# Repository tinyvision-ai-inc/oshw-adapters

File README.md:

# oshw-adapters
Various adapters for GPIO, MIPI etc.

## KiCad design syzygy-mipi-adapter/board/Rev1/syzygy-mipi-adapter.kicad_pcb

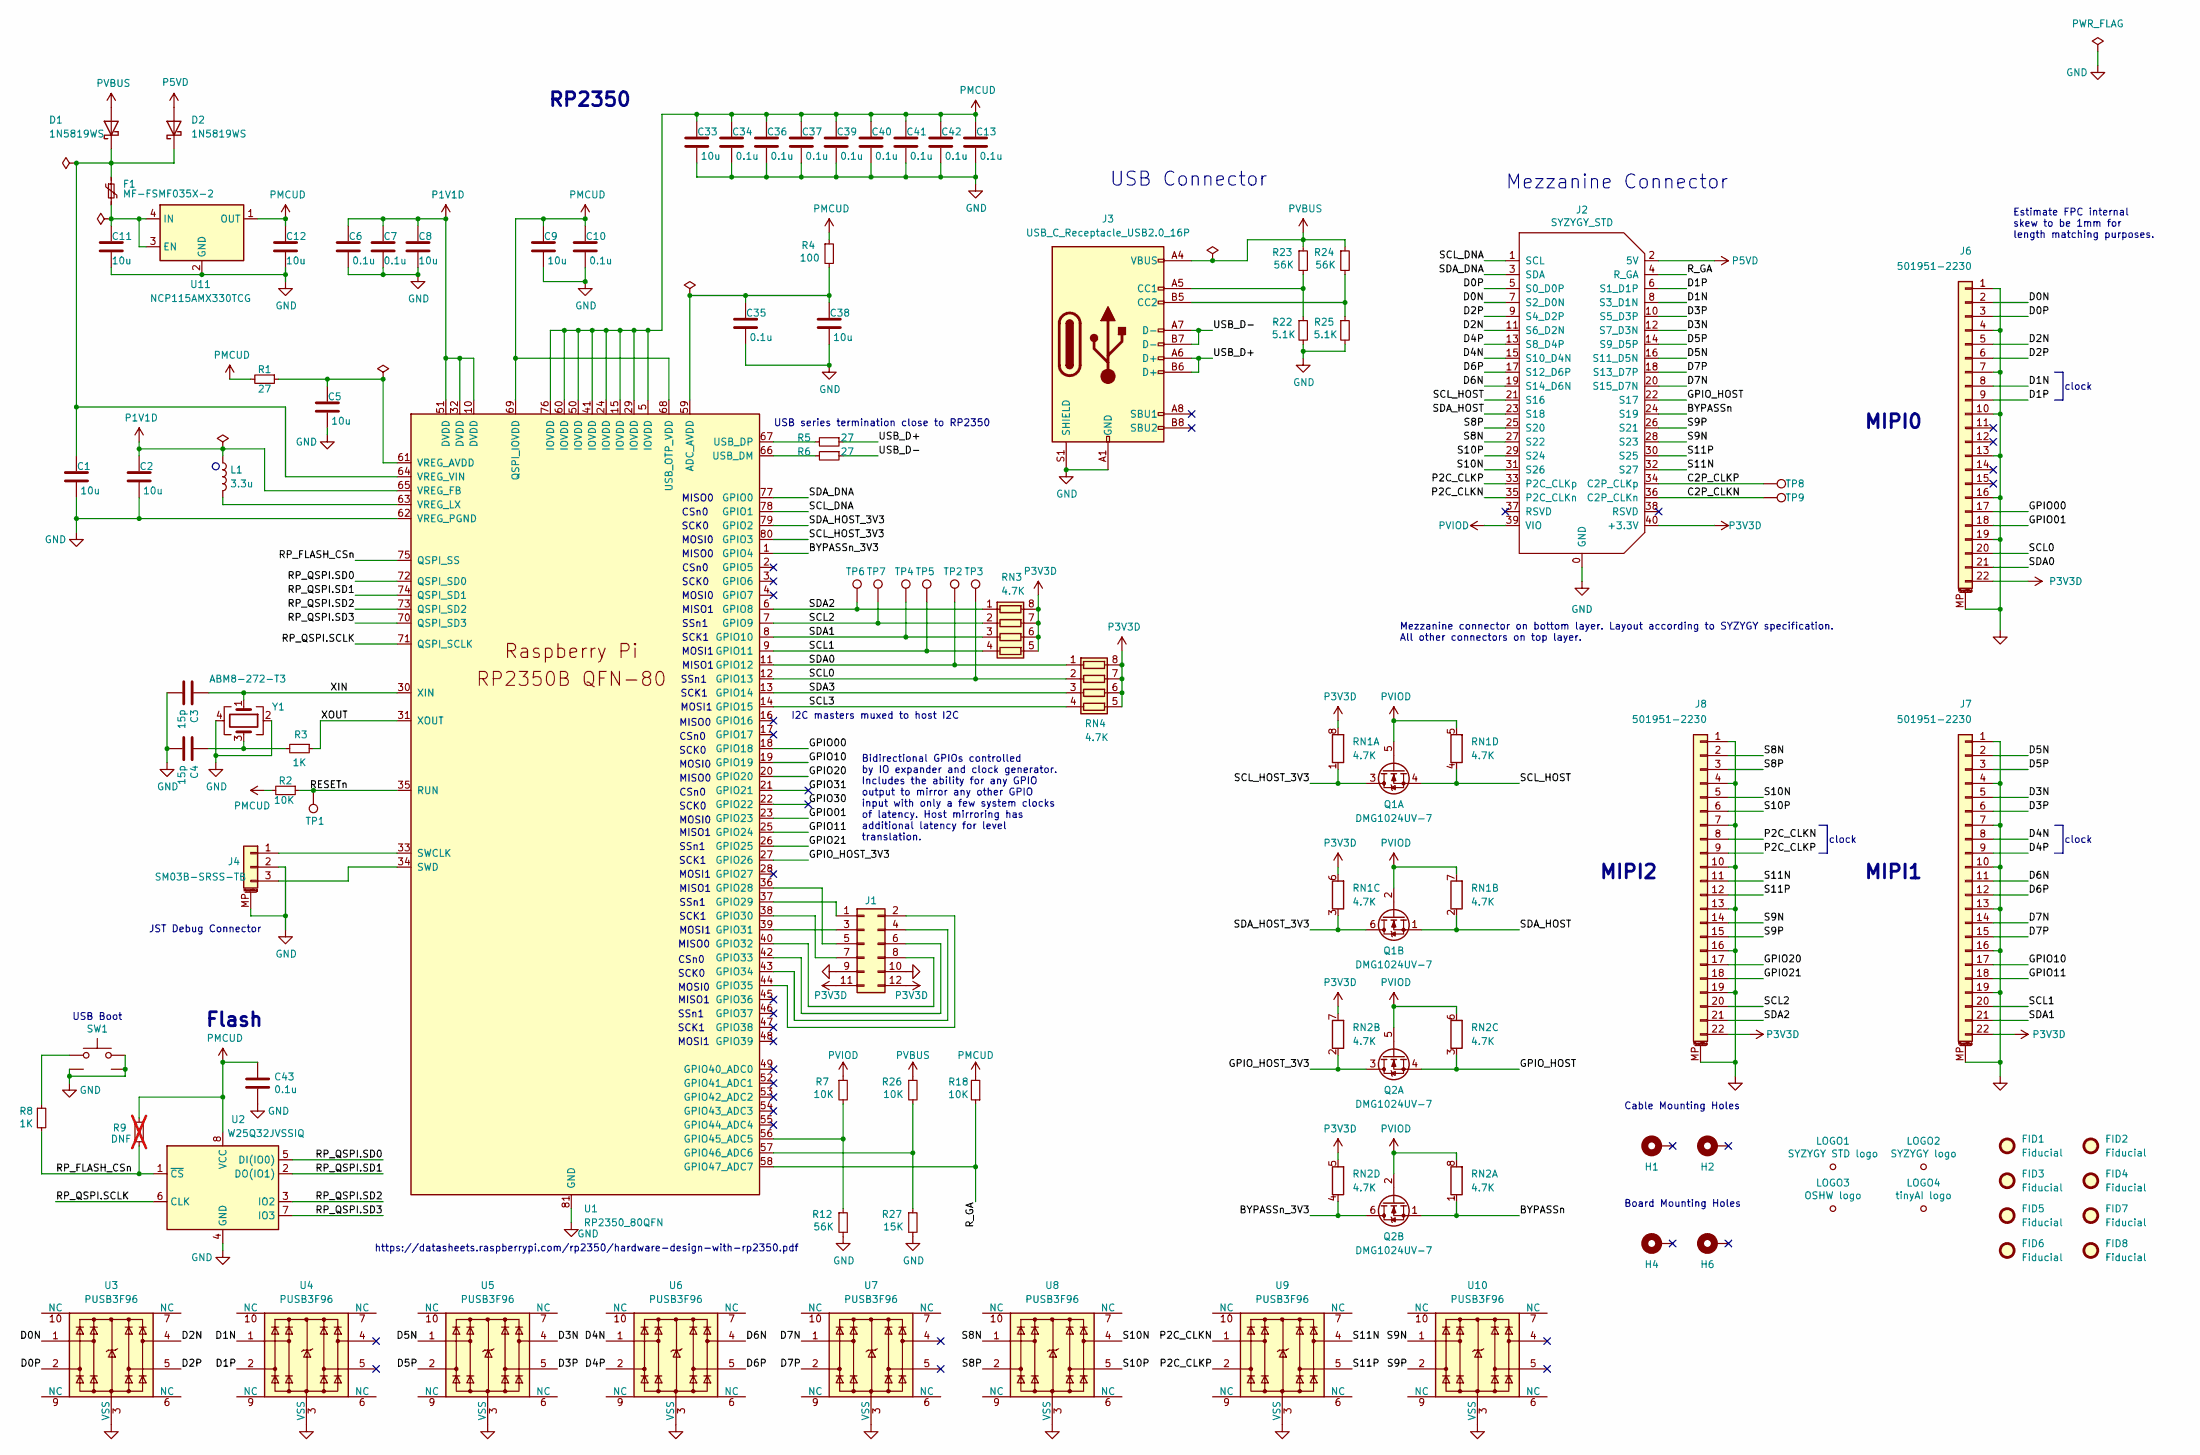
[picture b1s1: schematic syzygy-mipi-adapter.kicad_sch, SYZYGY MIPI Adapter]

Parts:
C1, C2, C5, C8, C9, C11, C12, C33: 10u; C_0402_1005Metric; MPN GRM155R60J475ME87D
C3, C4: 15p; C_0201_0603Metric; MPN GRM1555C1E150JA01D
C6, C7, C10, C13, C34, C35, C36, C37, C39, C40, C41, C42, C43: 0.1u; C_0201_0603Metric; MPN GRM155R71C104KA88J
C38: 10u; C_0402_1005Metric; MPN GRM155R71C104KA88J
D1, D2: 1N5819WS; D_SOD-323
F1: MF-FSMF035X-2; R_0603_1608Metric
FID1, FID2, FID3, FID4, FID5, FID6, FID7, FID8: Fiducial; Fiducial_0.75mm_Mask1.5mm
H1, H2, H4, H6: MountingHole_Pad; MountingHole_3.2mm_M3_6.5mm_Pad_TopBottom
J1: Conn_02x06_Odd_Even; PinHeader_2x06_P2.54mm_Vertical
J2: SYZYGY_STD; QTE-020-01-F-D-A; Manufacturer_PN QTE-020-01-F-D-A
J3: USB_C_Receptacle_USB2.0_16P; USB_C_Receptacle_HRO_TYPE-C-31-M-12
J4: SM03B-SRSS-TB; JST_SH_SM03B-SRSS-TB_1x03-1MP_P1.00mm_Horizontal; MPN SM03B-SRSS-TB
J6, J7, J8: 501951-2230
L1: 3.3u; L_pol_2016; MPN MLP2016H3R3MT0S1
LOGO1: SYZYGY STD logo; SYZYGY_STD_Logo; MPN DNP; Digi-Key_PN DNP
LOGO2: SYZYGY logo; SYZYGY_Logo; MPN DNP; Digi-Key_PN DNP
LOGO3: OSHW logo; OSHW_Dual_0.1_Scale_2140; MPN DNP; Digi-Key_PN DNP
LOGO4: tinyAI logo; tinyAI_4_5mm; MPN DNP; Digi-Key_PN DNP
Q1, Q2: DMG1024UV-7; SOT-563
R1, R5, R6: 27; R_0402_1005Metric; MPN RC0402FR-0727RL
R2, R7, R26: 10K; R_0402_1005Metric; MPN RC0402FR-0727RL
R3, R8: 1K; R_0402_1005Metric; MPN RC0402FR-071KL
R4: 100; R_0402_1005Metric; MPN RC0402FR-0727RL
R9: DNF; R_0402_1005Metric; not fitted
R12, R23, R24: 56K; R_0402_1005Metric; MPN RC0402FR-0727RL
R18: 10K; R_0402_1005Metric
R22, R25: 5.1K; R_0402_1005Metric; MPN RC0402FR-0727RL
R27: 15K; R_0402_1005Metric; MPN RC0402FR-0727RL
RN1, RN2, RN3, RN4: 4.7K; R_Array_Concave_4x0402
SW1: PTS820J25KSMTRLFS
TP1, TP2, TP3, TP4, TP5, TP6, TP7, TP8, TP9: TestPoint; TestPoint_Pad_1.0x1.0mm
U1: RP2350_80QFN; RP2350B_QFN-80_EP_10.573x10.573_Pitch0.4mm
U2: W25Q32JVSSIQ; SOIC-8_5.3x5.3mm_P1.27mm; MPN W25Q32JVSSIQ
U3, U4, U5, U6, U7, U8, U9, U10: PUSB3F96; PUSB3F96X
U11: NCP115AMX330TCG; OnSemi_XDFN4-1EP_1.0x1.0mm_EP0.52x0.52mm
Y1: ABM8-272-T3; Crystal_SMD_3225-4Pin_3.2x2.5mm; MPN ABM8-272-T3

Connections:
/BYPASSn: J2.24 (S19), Q2.1 (S), RN2.1 (R1.1)
/BYPASSn_3V3: Q2.6 (D), RN2.4 (R4.1), U1.1 (GPIO4)
/C2P_CLKN: J2.36 (C2P_CLKn), TP9.1
/C2P_CLKP: J2.34 (C2P_CLKp), TP8.1
/D0N: J2.7 (S2_D0N), J6.2, U3.1
/D0P: J2.5 (S0_D0P), J6.3, U3.2
/D1N: J2.8 (S3_D1N), J6.8, U4.1
/D1P: J2.6 (S1_D1P), J6.9, U4.2
/D2N: J2.11 (S6_D2N), J6.5, U3.4
/D2P: J2.9 (S4_D2P), J6.6, U3.5
/D3N: J2.12 (S7_D3N), J7.5, U5.4
/D3P: J2.10 (S5_D3P), J7.6, U5.5
/D4N: J2.15 (S10_D4N), J7.8, U6.1
/D4P: J2.13 (S8_D4P), J7.9, U6.2
/D5N: J2.16 (S11_D5N), J7.2, U5.1
/D5P: J2.14 (S9_D5P), J7.3, U5.2
/D6N: J2.19 (S14_D6N), J7.11, U6.4
/D6P: J2.17 (S12_D6P), J7.12, U6.5
/D7N: J2.20 (S15_D7N), J7.14, U7.1
/D7P: J2.18 (S13_D7P), J7.15, U7.2
/GPIO00: J6.17, U1.18 (GPIO18)
/GPIO01: J6.18, U1.23 (GPIO23)
/GPIO10: J7.17, U1.19 (GPIO19)
/GPIO11: J7.18, U1.25 (GPIO24)
/GPIO20: J8.17, U1.20 (GPIO20)
/GPIO21: J8.18, U1.26 (GPIO25)
/GPIO30: U1.22 (GPIO22)
/GPIO31: U1.21 (GPIO21)
/GPIO_HOST: J2.22 (S17), Q2.4 (S), RN2.3 (R3.1)
/GPIO_HOST_3V3: Q2.3 (D), RN2.2 (R2.1), U1.27 (GPIO26)
/P2C_CLKN: J2.35 (P2C_CLKn), J8.8, U9.1
/P2C_CLKP: J2.33 (P2C_CLKp), J8.9, U9.2
/RESETn: R2.1, TP1.1, U1.35 (RUN)
/RP_FLASH_CSn: R8.2, R9.1, U1.75 (QSPI_SS), U2.1 (~CS)
/RP_QSPI.SCLK: U1.71 (QSPI_SCLK), U2.6 (CLK)
/RP_QSPI.SD0: U1.72 (QSPI_SD0), U2.5 (DI(IO0))
/RP_QSPI.SD1: U1.74 (QSPI_SD1), U2.2 (DO(IO1))
/RP_QSPI.SD2: U1.73 (QSPI_SD2), U2.3 (IO2)
/RP_QSPI.SD3: U1.70 (QSPI_SD3), U2.7 (IO3)
/R_GA: J2.4 (R_GA), R18.1, U1.58 (GPIO47_ADC7)
/S8N: J2.27 (S22), J8.2, U8.1
/S8P: J2.25 (S20), J8.3, U8.2
/S9N: J2.28 (S23), J8.14, U10.1
/S9P: J2.26 (S21), J8.15, U10.2
/S10N: J2.31 (S26), J8.5, U8.4
/S10P: J2.29 (S24), J8.6, U8.5
/S11N: J2.32 (S27), J8.11, U9.4
/S11P: J2.30 (S25), J8.12, U9.5
/SCL0: J6.20, RN4.2 (R2.1), TP3.1, U1.12 (GPIO13)
/SCL1: J7.20, RN3.4 (R4.1), TP5.1, U1.9 (GPIO11)
/SCL2: J8.20, RN3.2 (R2.1), TP7.1, U1.7 (GPIO9)
/SCL3: RN4.4 (R4.1), U1.14 (GPIO15)
/SCL_DNA: J2.1 (SCL), U1.78 (GPIO1)
/SCL_HOST: J2.21 (S16), Q1.4 (S), RN1.4 (R4.1)
/SCL_HOST_3V3: Q1.3 (D), RN1.1 (R1.1), U1.80 (GPIO3)
/SDA0: J6.21, RN4.1 (R1.1), TP2.1, U1.11 (GPIO12)
/SDA1: J7.21, RN3.3 (R3.1), TP4.1, U1.8 (GPIO10)
/SDA2: J8.21, RN3.1 (R1.1), TP6.1, U1.6 (GPIO8)
/SDA3: RN4.3 (R3.1), U1.13 (GPIO14)
/SDA_DNA: J2.3 (SDA), U1.77 (GPIO0)
/SDA_HOST: J2.23 (S18), Q1.1 (S), RN1.2 (R2.1)
/SDA_HOST_3V3: Q1.6 (D), RN1.3 (R3.1), U1.79 (GPIO2)
/USB_D+: J3.A6 (D+), J3.B6 (D+), R5.1
/USB_D-: J3.A7 (D-), J3.B7 (D-), R6.1
/XIN: C3.1, U1.30 (XIN), Y1.1
/XOUT: R3.1, U1.31 (XOUT)
GND: C1.2, C2.2, C3.2, C4.2, C5.2, C6.2, C7.2, C8.2, C9.2, C10.2, C11.2, C12.2, C13.2, C33.2, C34.2, C35.2, C36.2, C37.2, C38.2, C39.2, C40.2, C41.2, C42.2, C43.2, J1.9, J1.10, J2.0 (GND), J3.A1 (GND), J3.A12 (GND), J3.B1 (GND), J3.B12 (GND), J3.S1 (SHIELD), J4.2, J4.MP (MountPin), J6.1, J6.4, J6.7, J6.10, J6.13, J6.16, J6.19, J6.MP (MountPin), J7.1, J7.4, J7.7, J7.10, J7.13, J7.16, J7.19, J7.MP (MountPin), J8.1, J8.4, J8.7, J8.10, J8.13, J8.16, J8.19, J8.MP (MountPin), R12.2, R22.2, R25.2, R27.2, SW1.1, SW1.SH1, SW1.SH2, U1.62 (VREG_PGND), U1.81 (GND), U2.4 (GND), U3.3 (VSS), U3.8 (VSS), U4.3 (VSS), U4.8 (VSS), U5.3 (VSS), U5.8 (VSS), U6.3 (VSS), U6.8 (VSS), U7.3 (VSS), U7.8 (VSS), U8.3 (VSS), U8.8 (VSS), U9.3 (VSS), U9.8 (VSS), U10.3 (VSS), U10.8 (VSS), U11.2 (GND), U11.5 (GND), Y1.2, Y1.4
unnamed: C4.1, R3.2, Y1.3
unnamed: C1.1, D1.1 (K), D2.1 (K), F1.1, U1.64 (VREG_VIN)
unnamed: J1.1, U1.37 (GPIO29)
unnamed: J1.2, U1.44 (GPIO35)
unnamed: J1.3, U1.39 (GPIO31)
unnamed: J1.4, U1.43 (GPIO34)
unnamed: J1.5, U1.36 (GPIO28)
unnamed: J1.6, U1.42 (GPIO33)
unnamed: J1.7, U1.38 (GPIO30)
unnamed: J1.8, U1.40 (GPIO32)
unnamed: J3.A5 (CC1), R22.1, R23.2
unnamed: J3.B5 (CC2), R24.2, R25.1
unnamed: J4.1, U1.33 (SWCLK)
unnamed: J4.3, U1.34 (SWD)
unnamed: R8.1, SW1.2
unnamed: C35.1, C38.1, R4.2, U1.59 (ADC_AVDD)
unnamed: R7.2, R12.1, U1.56 (GPIO45_ADC5)
unnamed: R26.2, R27.1, U1.57 (GPIO46_ADC6)
unnamed: R6.2, U1.66 (USB_DM)
unnamed: R5.2, U1.67 (USB_DP)
unnamed: C5.1, R1.1, U1.61 (VREG_AVDD)
unnamed: L1.2, U1.63 (VREG_LX)
unnamed: C11.1, F1.2, U11.3 (EN), U11.4 (IN)
P1V1D: C2.1, C6.1, C7.1, C8.1, L1.1, U1.10 (DVDD), U1.32 (DVDD), U1.51 (DVDD), U1.65 (VREG_FB)
P3V3D: J1.11, J1.12, J2.40 (+3.3V), J6.22, J7.22, J8.22, RN1.6 (R3.2), RN1.8 (R1.2), RN2.5 (R4.2), RN2.7 (R2.2), RN3.5 (R4.2), RN3.6 (R3.2), RN3.7 (R2.2), RN3.8 (R1.2), RN4.5 (R4.2), RN4.6 (R3.2), RN4.7 (R2.2), RN4.8 (R1.2)
P5VD: D2.2 (A), J2.2 (5V)
PMCUD: C9.1, C10.1, C12.1, C13.1, C33.1, C34.1, C36.1, C37.1, C39.1, C40.1, C41.1, C42.1, C43.1, R1.2, R2.2, R4.1, R9.2, R18.2, U1.5 (IOVDD), U1.15 (IOVDD), U1.24 (IOVDD), U1.29 (IOVDD), U1.41 (IOVDD), U1.50 (IOVDD), U1.60 (IOVDD), U1.68 (USB_OTP_VDD), U1.69 (QSPI_IOVDD), U1.76 (IOVDD), U2.8 (VCC), U11.1 (OUT)
PVBUS: D1.2 (A), J3.A4 (VBUS), J3.A9 (VBUS), J3.B4 (VBUS), J3.B9 (VBUS), R23.1, R24.1, R26.1
PVIOD: J2.39 (VIO), Q1.2 (G), Q1.5 (G), Q2.2 (G), Q2.5 (G), R7.1, RN1.5 (R4.2), RN1.7 (R2.2), RN2.6 (R3.2), RN2.8 (R1.2)

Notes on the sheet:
USB Boot
SSn1
RP2350
MISO0
SCK1
I2C masters muxed to host I2C
MISO1
MIPI0
CSn0
MOSI1
MOSI0
MIPI2
Board Mounting Holes
Estimate FPC internal skew to be 1mm for length matching purposes.
clock
USB Connector
Bidirectional GPIOs controlled by IO expander and clock generator. Includes the ability for any GPIO output to mirror any other GPIO input with only a few system clocks of latency. Host mirroring has additional latency for level translation.
SCK0
Flash
Mezzanine connector on bottom layer. Layout according to SYZYGY specification. All other connectors on top layer.
JST Debug Connector
Mezzanine Connector
Cable Mounting Holes
USB series termination close to RP2350
https://datasheets.raspberrypi.com/rp2350/hardware-design-with-rp2350.pdf
MIPI1

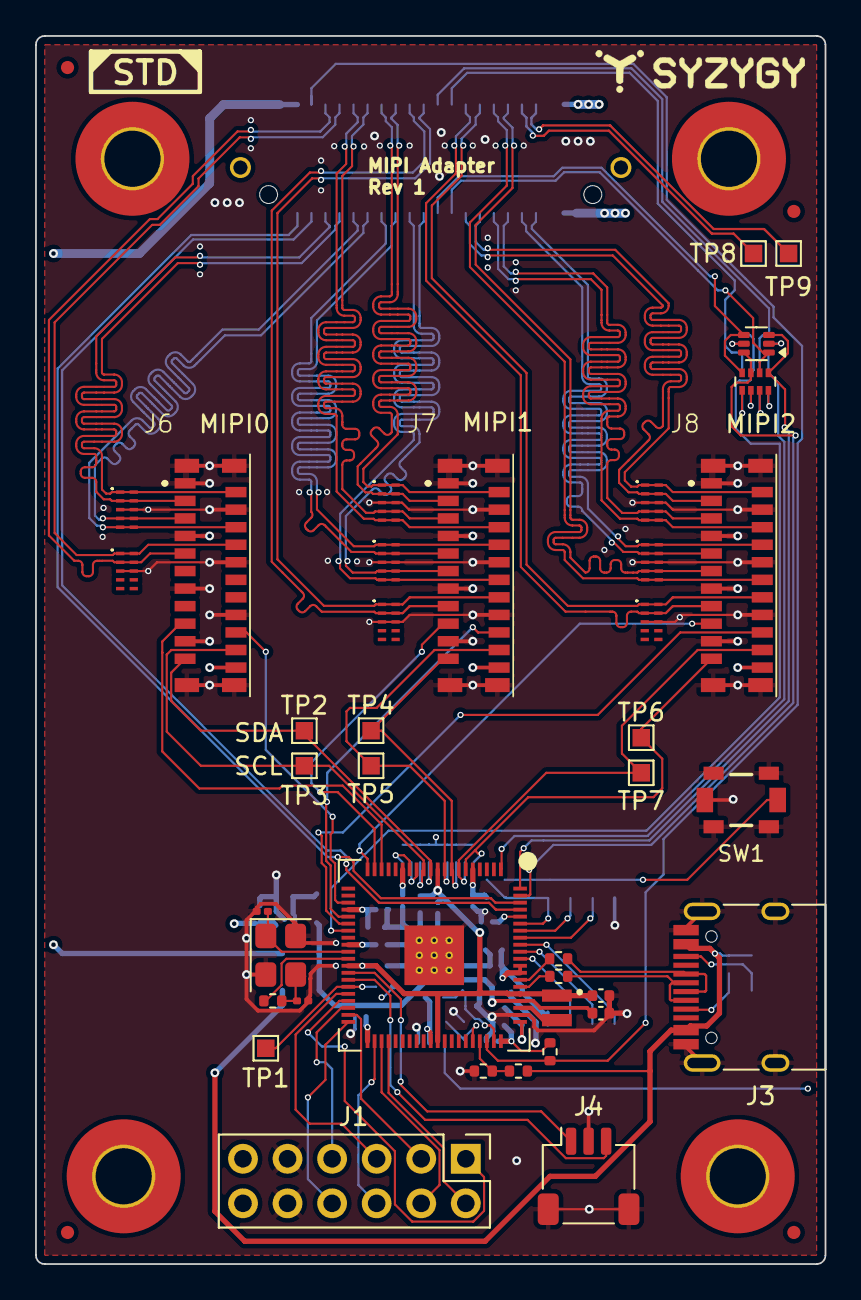
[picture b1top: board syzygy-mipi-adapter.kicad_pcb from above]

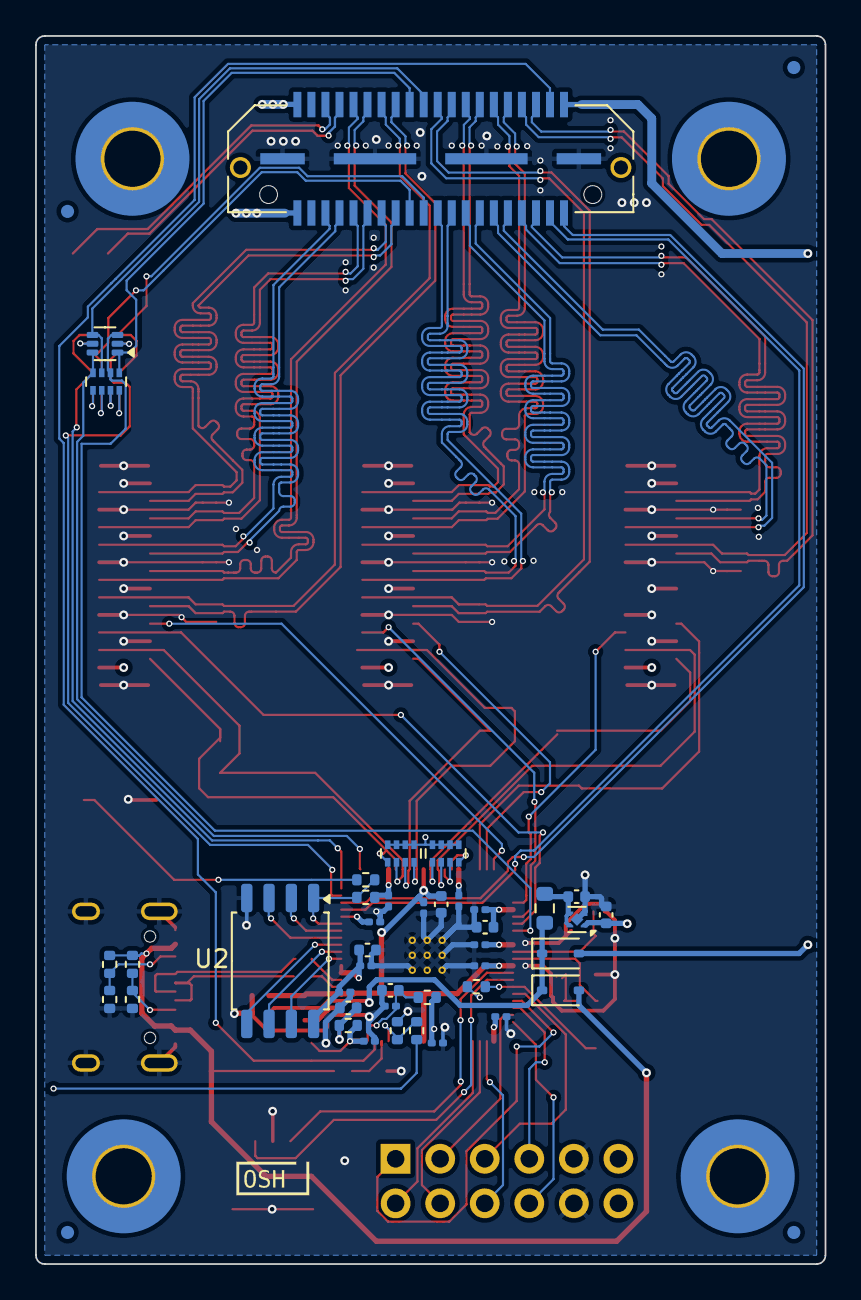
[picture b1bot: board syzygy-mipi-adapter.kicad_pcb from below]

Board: 4 copper layers, 45.0 x 70.0 mm, 96 parts (45 on the bottom side), 94 nets.

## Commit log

2025-08-24 initial version
2025-08-26 fixes
2025-08-26 Plot schematic
2025-08-26 Restore accidentally deleted mounting hole
2025-08-26 Fix length matching of diff pair
2025-08-27 Fix fill zones
2025-08-28 Add USB connector and 3.3V regulator to Syzygy MIPI adapter
2025-08-28 Fix schematic ERC errors for Syzygy MIPI adapter
2025-08-28 Add USB connector and 3.3V regulator
2025-08-29 Add I2C test pads
2025-09-01 Cut out power planes under differential pair pads
2025-09-01 Oscillator ground shielding. Improve USB routing.
2025-09-02 Sort out decoupling caps
2025-09-02 Separate 3.3V rails for MSU vs Syzygy
2025-09-02 Added test points for otherwise unconnected Syzygy pins
2025-09-02 Refill zones
2025-09-02 Remove P5VD trace between Syzygy connector and left fill to open up 3.3V plane
2025-09-02 Reduce length of PVIOD trace between Syzygy connector and right fill to open up 3.3V plane
2025-09-02 Update fills
2025-09-04 Update stack-up. Adjust DP trace width and spacing to 100 ohm impedance.
2025-09-04 Replace only 2.2u cap with 10u
2025-09-04 Made tinyvision logo bigger
2025-09-06 Add a few more vias
2025-11-05 Move files to board/Rev0
2025-11-05 Rev 1 of Syzygy MIPI adapter (currently just a copy of Rev 0)
2025-11-05 Consolidate footprints from several footprint libraries into CUSTOM.pretty
2025-11-05 Fix issue #5 as described in that issue
2025-11-05 Fix issue #7
2025-11-05 Fix issue #6 and other silkscreen issues. Moved I2C test points a bit further away from FPCs.
